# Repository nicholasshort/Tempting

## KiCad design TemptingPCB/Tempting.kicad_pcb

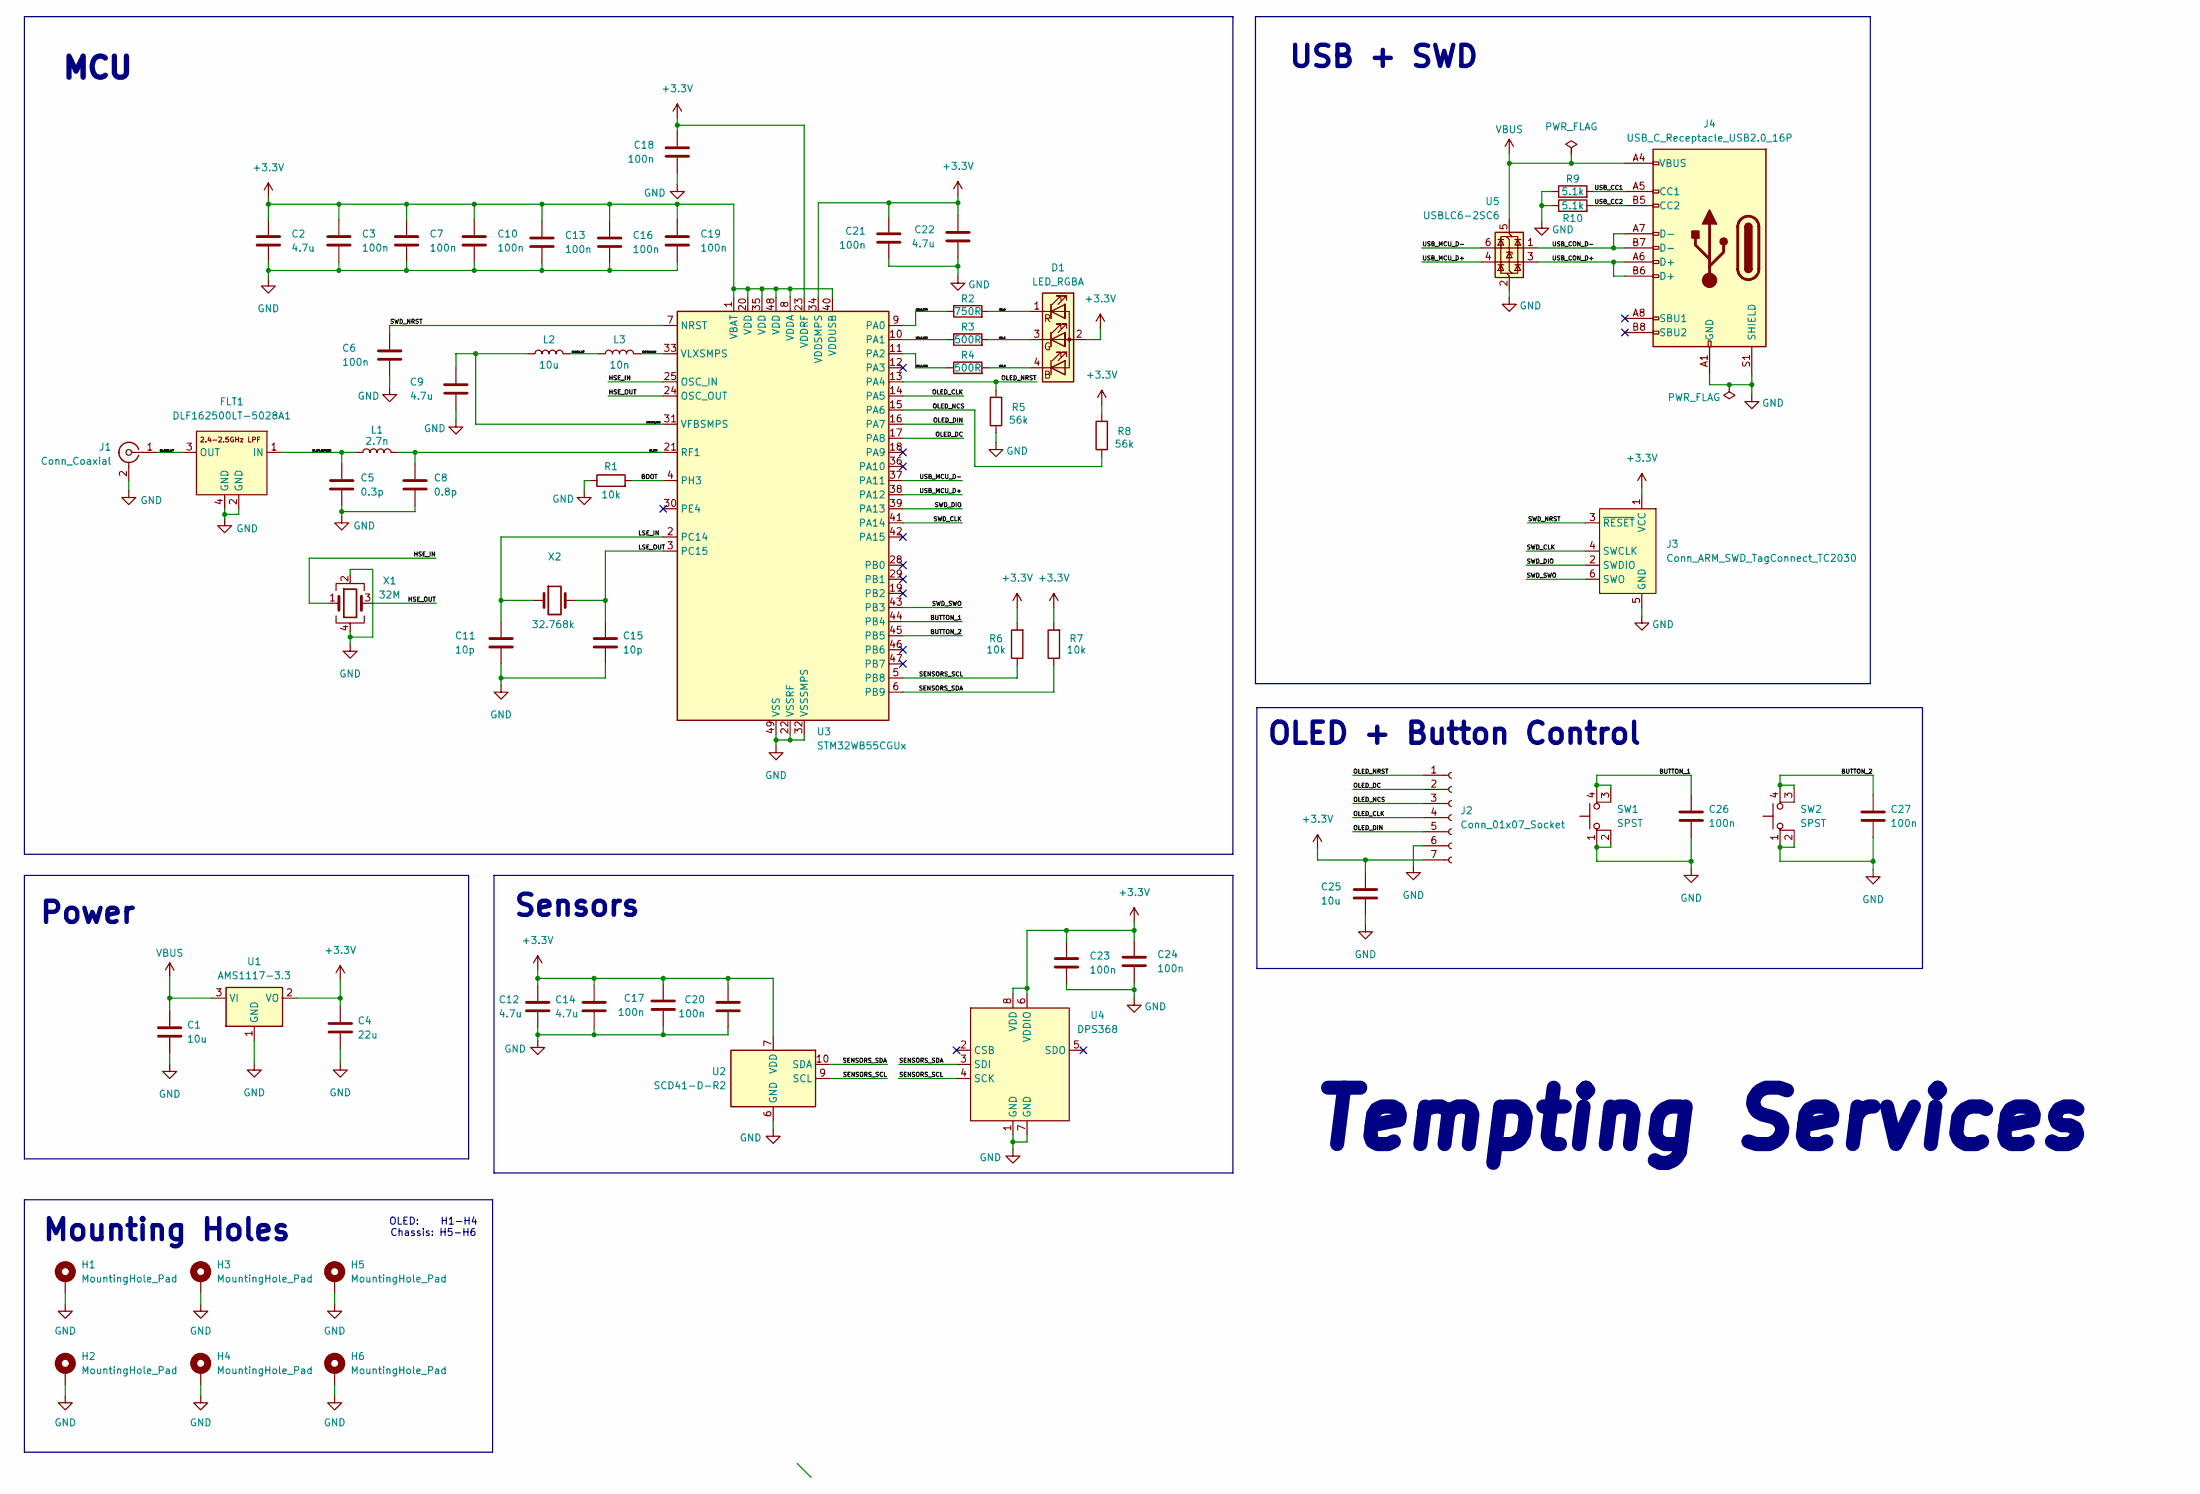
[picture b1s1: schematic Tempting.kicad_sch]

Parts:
C1, C25: 10u; C_0805_2012Metric; JLCPCB Part # C15850
C2, C9, C12, C14, C22: 4.7u; C_0603_1608Metric; JLCPCB Part # C1705
C3, C6, C7, C10, C13, C16, C17, C18, C19, C20, C21, C23, C24, C26, C27: 100n; C_0402_1005Metric; JLCPCB Part # C1525
C4: 22u; C_0805_2012Metric; JLCPCB Part # C29277
C5: 0.3p; C_0402_1005Metric; JLCPCB Part # C880415
C8: 0.8p; C_0402_1005Metric; JLCPCB Part # C76915
C11, C15: 10p; C_0402_1005Metric; JLCPCB Part # C161145
D1: LED_RGBA; AAA3528LSEEZGKQBKS; JLCPCB Part # C5547384
FLT1: DLF162500LT-5028A1; JLCPCB Part # C531364
H1, H2, H3, H4: MountingHole_Pad; MountingHole_2.2mm_M2_Pad_Via
H5, H6: MountingHole_Pad; MountingHole_3.2mm_M3_Pad_Via
J1: Conn_Coaxial; SMA_Samtec_SMA-J-P-H-ST-EM1_EdgeMount; JLCPCB Part # C5199907
J2: Conn_01x07_Socket; PinSocket_1x07_P2.54mm_Vertical
J3: Conn_ARM_SWD_TagConnect_TC2030; Tag-Connect_TC2030-IDC-FP_2x03_P1.27mm_Vertical
J4: USB_C_Receptacle_USB2.0_16P; USB_C_Receptacle_HRO_TYPE-C-31-M-12; JLCPCB Part # C165948
L1: 2.7n; L_0402_1005Metric; JLCPCB Part # C77108
L2: 10u; L_0805_2012Metric; JLCPCB Part # C98030
L3: 10n; L_0402_1005Metric; JLCPCB Part # C76760
R1, R6, R7: 10k; R_0402_1005Metric; JLCPCB Part # C25744
R2: 750R; R_0402_1005Metric; JLCPCB Part # C25132
R3, R4: 500R; R_0402_1005Metric; JLCPCB Part # C4125
R5, R8: 56k; R_0402_1005Metric; JLCPCB Part # C25796
R9, R10: 5.1k; R_0402_1005Metric; JLCPCB Part # C25905
SW1, SW2: SPST; 2-1825910-7; JLCPCB Part # C513492
U1: AMS1117-3.3; SOT-223-3_TabPin2; JLCPCB Part # C6186
U2: SCD41-D-R2; Sensirion_SCD4x-1EP_10.1x10.1mm_P1.25mm_EP4.8x4.8mm; JLCPCB Part # C3659362
U3: STM32WB55CGUx; QFN-48-1EP_7x7mm_P0.5mm_EP5.6x5.6mm; JLCPCB Part # C404023
U4: DPS368; JLCPCB Part # C3232508
U5: USBLC6-2SC6; SOT-23-6; JLCPCB Part # C7519
X1: 32M; Crystal_SMD_2016-4Pin_2.0x1.6mm; JLCPCB Part # C1986260
X2: 32.768k; Crystal_SMD_2012-2Pin_2.0x1.2mm; JLCPCB Part # C528982

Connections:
+3.3V: C2.1, C3.1, C4.1, C7.1, C10.1, C12.1, C13.1, C14.1, C16.1, C17.1, C18.1, C19.1, C20.1, C21.1, C22.1, C23.1, C24.1, C25.1, D1.2 (A), J2.7, J3.1 (VCC), R6.2, R7.2, R8.2, U1.2 (VO), U2.7 (VDD), U2.19 (VDD), U3.1 (VBAT), U3.8 (VDDA), U3.20 (VDD), U3.23 (VDDRF), U3.34 (VDDSMPS), U3.35 (VDD), U3.40 (VDDUSB), U3.48 (VDD), U4.6 (VDDIO), U4.8 (VDD)
/BOOT: R1.2, U3.4 (PH3)
/BUTTON_1: C26.1, SW1.3 (K), SW1.4 (A), U3.44 (PB4)
/BUTTON_2: C27.1, SW2.3 (K), SW2.4 (A), U3.45 (PB5)
/HSE_IN: U3.25 (OSC_IN), X1.1
/HSE_OUT: U3.24 (OSC_OUT), X1.3
/LED_B: D1.4 (BK), R4.2
/LED_B_MCU: R4.1, U3.11 (PA2)
/LED_G: D1.3 (GK), R3.2
/LED_G_MCU: R3.1, U3.10 (PA1)
/LED_R: D1.1 (RK), R2.2
/LED_R_MCU: R2.1, U3.9 (PA0)
/LSE_IN: C11.1, U3.2 (PC14), X2.1
/LSE_OUT: C15.1, U3.3 (PC15), X2.2
/OLED_CLK: J2.4, U3.14 (PA5)
/OLED_DC: J2.2, U3.17 (PA8)
/OLED_DIN: J2.5, U3.16 (PA7)
/OLED_NCS: J2.3, R8.1, U3.15 (PA6)
/OLED_NRST: J2.1, R5.2, U3.13 (PA4)
/RF_COAX_LPF: FLT1.3 (OUT), J1.1 (In)
/RF_LPF_MATCHING: C5.1, FLT1.1 (IN), L1.1
/RF_MCU: C8.1, L1.2, U3.21 (RF1)
/SENSORS_SCL: R6.1, U2.9 (SCL), U3.5 (PB8), U4.4 (SCK)
/SENSORS_SDA: R7.1, U2.10 (SDA), U3.6 (PB9), U4.3 (SDI)
/SMPSFB_MCU: C9.1, L2.1, U3.31 (VFBSMPS)
/SMPSLX_INT: L2.2, L3.1
/SMPSLX_MCU: L3.2, U3.33 (VLXSMPS)
/SWD_CLK: J3.4 (SWCLK), U3.41 (PA14)
/SWD_DIO: J3.2 (SWDIO), U3.39 (PA13)
/SWD_NRST: C6.1, J3.3 (~RESET), U3.7 (NRST)
/SWD_SWO: J3.6 (SWO), U3.43 (PB3)
/USB_CC1: J4.A5 (CC1), R9.2
/USB_CC2: J4.B5 (CC2), R10.2
/USB_CON_D+: J4.A6 (D+), J4.B6 (D+), U5.3 (I/O2)
/USB_CON_D-: J4.A7 (D-), J4.B7 (D-), U5.1 (I/O1)
/USB_MCU_D+: U3.38 (PA12), U5.4 (I/O2)
/USB_MCU_D-: U3.37 (PA11), U5.6 (I/O1)
GND: C1.2, C2.2, C3.2, C4.2, C5.2, C6.2, C7.2, C8.2, C9.2, C10.2, C11.2, C12.2, C13.2, C14.2, C15.2, C16.2, C17.2, C18.2, C19.2, C20.2, C21.2, C22.2, C23.2, C24.2, C25.2, C26.2, C27.2, FLT1.2 (GND), FLT1.4 (GND), H1.1, H2.1, H3.1, H4.1, H5.1, H6.1, J1.2 (Ext), J2.6, J3.5 (GND), J4.A1 (GND), J4.A12 (GND), J4.B1 (GND), J4.B12 (GND), J4.S1 (SHIELD), R1.1, R5.1, R9.1, R10.1, SW1.1, SW1.2, SW2.1, SW2.2, U1.1 (GND), U2.6 (GND), U2.20 (GND), U2.21 (GND), U3.22 (VSSRF), U3.32 (VSSSMPS), U3.49 (VSS), U4.1 (GND), U4.7 (GND), U5.2 (GND), X1.2, X1.4
VBUS: C1.1, J4.A4 (VBUS), J4.A9 (VBUS), J4.B4 (VBUS), J4.B9 (VBUS), U1.3 (VI), U5.5 (VBUS)

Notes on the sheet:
Tempting Services
MCU
USB + SWD
Mounting Holes
Power
Sensors
OLED + Button Control
OLED: H1-H4 Chassis: H5-H6

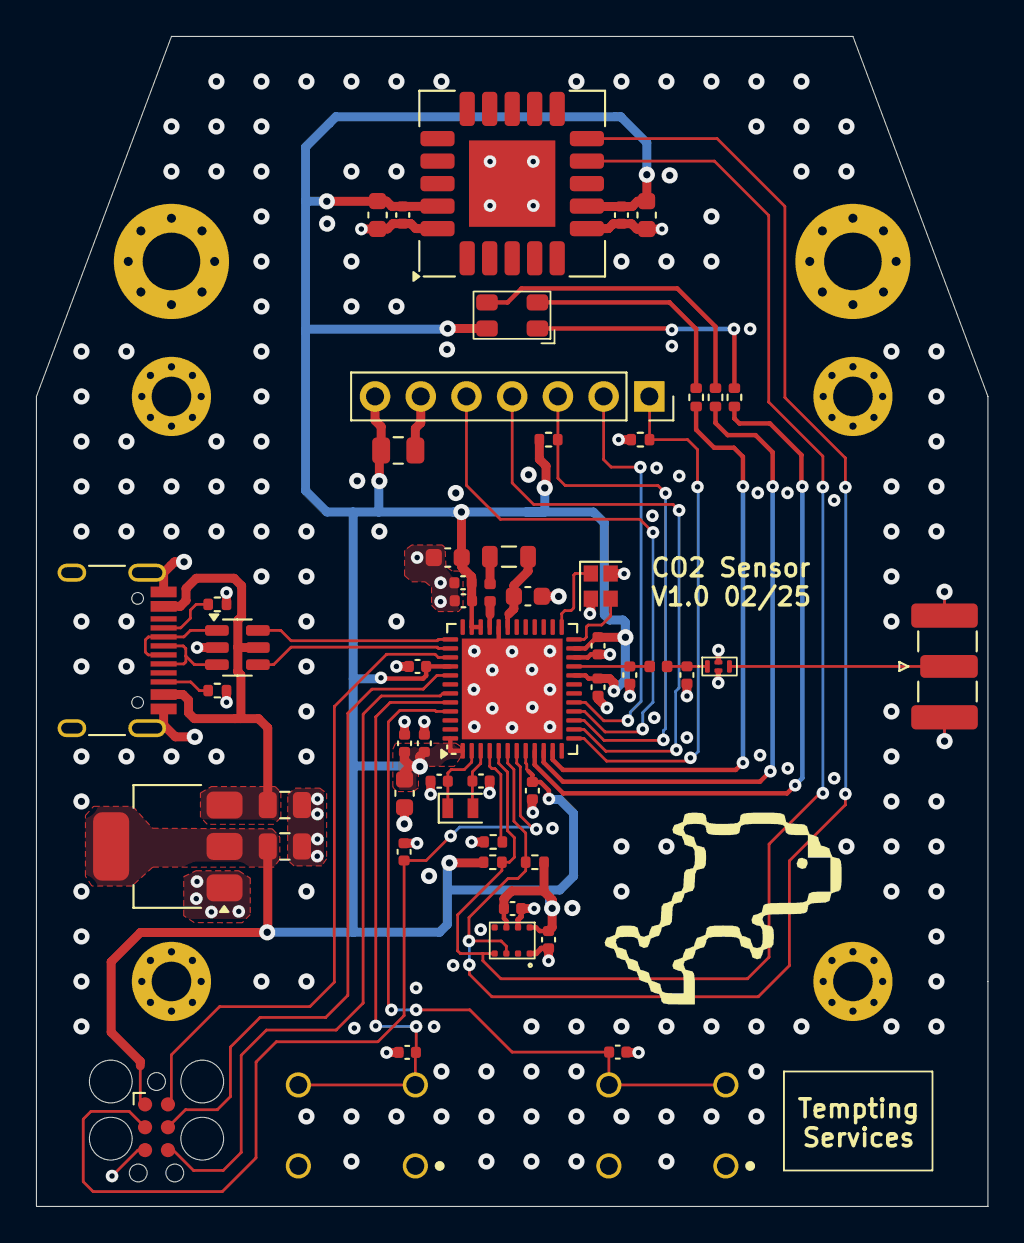
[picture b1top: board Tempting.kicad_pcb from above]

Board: 4 copper layers, 52.9 x 65.0 mm, 61 parts (0 on the bottom side), 39 nets.

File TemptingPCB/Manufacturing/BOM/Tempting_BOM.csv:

"Reference","Value","Footprint","JLCPCB Part #"
"C1,C25","10u","Capacitor_SMD:C_0805_2012Metric","C15850"
"C2,C9,C12,C14,C22","4.7u","Capacitor_SMD:C_0603_1608Metric","C1705"
"C3,C6,C7,C10,C13,C16,C17,C18,C19,C20,C21,C23,C24,C26,C27","100n","Capacitor_SMD:C_0402_1005Metric","C1525"
"C4","22u","Capacitor_SMD:C_0805_2012Metric","C29277"
"C5","0.3p","Capacitor_SMD:C_0402_1005Metric","C880415"
"C8","0.8p","Capacitor_SMD:C_0402_1005Metric","C76915"
"C11,C15","10p","Capacitor_SMD:C_0402_1005Metric","C161145"
"D1","LED_RGBA","Tempting_Footprint_Libraries:AAA3528LSEEZGKQBKS","C5547384"
"FLT1","DLF162500LT-5028A1","Tempting_Footprint_Libraries:DLF162500LT-5028A1","C531364"
"J1","Conn_Coaxial","Connector_Coaxial:SMA_Samtec_SMA-J-P-H-ST-EM1_EdgeMount","C5199907"
"J2","Conn_01x07_Socket","Connector_PinSocket_2.54mm:PinSocket_1x07_P2.54mm_Vertical",""
"J4","USB_C_Receptacle_USB2.0_16P","Connector_USB:USB_C_Receptacle_HRO_TYPE-C-31-M-12","C165948"
"L1","2.7n","Inductor_SMD:L_0402_1005Metric","C77108"
"L2","10u","Inductor_SMD:L_0805_2012Metric","C98030"
"L3","10n","Inductor_SMD:L_0402_1005Metric","C76760"
"R1,R6,R7","10k","Resistor_SMD:R_0402_1005Metric","C25744"
"R2","750R","Resistor_SMD:R_0402_1005Metric","C25132"
"R3,R4","500R","Resistor_SMD:R_0402_1005Metric","C4125"
"R5,R8","56k","Resistor_SMD:R_0402_1005Metric","C25796"
"R9,R10","5.1k","Resistor_SMD:R_0402_1005Metric","C25905"
"SW1,SW2","SPST","Tempting_Footprint_Libraries:2-1825910-7","C513492"
"U1","AMS1117-3.3","Package_TO_SOT_SMD:SOT-223-3_TabPin2","C6186"
"U2","SCD41-D-R2","Sensor:Sensirion_SCD4x-1EP_10.1x10.1mm_P1.25mm_EP4.8x4.8mm","C3659362"
"U3","STM32WB55CGUx","Package_DFN_QFN:QFN-48-1EP_7x7mm_P0.5mm_EP5.6x5.6mm","C404023"
"U4","DPS368","Tempting_Footprint_Libraries:DPS368","C3232508"
"U5","USBLC6-2SC6","Package_TO_SOT_SMD:SOT-23-6","C7519"
"X1","32M","Crystal:Crystal_SMD_2016-4Pin_2.0x1.6mm","C1986260"
"X2","32.768k","Crystal:Crystal_SMD_2012-2Pin_2.0x1.2mm","C528982"

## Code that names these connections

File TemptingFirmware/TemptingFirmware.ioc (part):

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Mcu.Name=STM32WB55CGUx
Mcu.Package=UFQFPN48
Mcu.UserName=STM32WB55CGUx
PA0.Signal=S_TIM2_CH1
PA1.Signal=S_TIM2_CH2
PA11.Mode=Device
PA11.Signal=USB_DM
PA12.Mode=Device
PA12.Signal=USB_DP
PA13.Mode=Trace_Asynchronous_SW
PA13.Signal=SYS_JTMS-SWDIO
PA14.Mode=Trace_Asynchronous_SW
PA14.Signal=SYS_JTCK-SWCLK
PA2.Signal=S_TIM2_CH3
PA4.GPIOParameters=GPIO_Label
PA4.GPIO_Label=OLED_NRST
PA4.Signal=GPIO_Output
PA5.Mode=TX_Only_Simplex_Unidirect_Master
PA5.Signal=SPI1_SCK
PA6.GPIOParameters=GPIO_Label
PA6.GPIO_Label=OLED_NCS
PA6.Signal=GPIO_Output
PA7.Mode=TX_Only_Simplex_Unidirect_Master
PA7.Signal=SPI1_MOSI
PA8.GPIOParameters=GPIO_Label
PA8.GPIO_Label=OLED_DC
PA8.Signal=GPIO_Output
PB3.Mode=Trace_Asynchronous_SW
PB3.Signal=SYS_JTDO-SWO
PB4.GPIOParameters=GPIO_PuPd,GPIO_ModeDefaultEXTI
PB4.GPIO_ModeDefaultEXTI=GPIO_MODE_IT_FALLING
PB4.GPIO_PuPd=GPIO_PULLUP
PB4.Signal=GPXTI4
PB5.GPIOParameters=GPIO_PuPd,GPIO_ModeDefaultEXTI
PB5.GPIO_ModeDefaultEXTI=GPIO_MODE_IT_FALLING
PB5.GPIO_PuPd=GPIO_PULLUP
PB5.Signal=GPXTI5
PB8.Mode=I2C
PB8.Signal=I2C1_SCL
PB9.Mode=I2C
PB9.Signal=I2C1_SDA
PC14-OSC32_IN.Mode=LSE-External-Oscillator
PC14-OSC32_IN.Signal=RCC_OSC32_IN
PC15-OSC32_OUT.Mode=LSE-External-Oscillator
PC15-OSC32_OUT.Signal=RCC_OSC32_OUT
RCC.HSE_VALUE=32000000
RCC.SYSCLKFreq_VALUE=64000000
RCC.SYSCLKSource=RCC_SYSCLKSOURCE_PLLCLK
board=custom

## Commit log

2025-02-05 Adding initial webpage
2025-02-05 Create CNAME
2025-02-05 Renamed tempting.html to index.html
2025-02-05 Added gitignore
2025-02-05 Updating gitignore
2025-02-05 Added decouplign capacitors to schematic
2025-02-05 Added crystals
2025-02-07 Added RF circuitry to schematic
2025-02-07 Added USB connector
2025-02-07 Added LDO
2025-02-07 Added OLED comm pins
2025-02-07 Added circuitry for SCD41
2025-02-12 Created symbol and footprint for DPS368
2025-02-12 Cleaned up and finished schematic
2025-02-13 Added new footprints and assigned all footprints
2025-02-13 Added all missing 3D models
2025-02-13 Added net classes
2025-02-13 Rough initial layout
2025-02-18 Added edge cuts and mounting holes
2025-02-18 Finetuned layout
2025-02-18 All signal traces routed
2025-02-19 Fixed DRC violations
2025-02-19 Assigned JLCPCB part numbers to all components
2025-02-19 Commit before ordering on jlc
2025-02-19 Adding manufacturing files
2025-02-27 Updated gerbers
2025-02-28 Updated ufl connector to sma
2025-02-28 Updating website
2025-02-28 Updating 3D model file
2025-05-03 Commit before recreating TempFirmware in cubeide
2025-06-16 Added zigbee capabilities to Tempting
2025-06-17 Working logs over VCP
2025-06-18 Working temperature and pressure attribute table updates. Learned that HAL_Delay cannot be used within an HW_TS callback function
2025-06-18 Working attribute reporting with ZHA
2025-06-21 CO2 Cluster now visible on ZHA, however having trouble writing to CO2 measure attribute
